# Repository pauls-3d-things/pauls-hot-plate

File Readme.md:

# SMD Soldering Station / Hotplate

**WARNING! If you have no experience wiring mains, do not proceed with this project. USE THIS INFORMATION YOUR OWN RISK!!**

## Support my projects ❤️

It takes me countless hours to prepare and document my projects. [You can support me by reading/recommending my books.](https://p3dt.net/books.html) Thank you!

## License

See `License` file. GPLv3.

## Introduction

This is a project to build a DIY PID controlled hotplate. This includes a python script to create a temperature chart and a tiny PCB to extend a TTGO 1.3" OLED shield as a controller.

- ESP8266 OLED board: https://www.aliexpress.com/item/32854542718.html
- SMD Hot plate, maybe something like this: https://www.aliexpress.com/item/1005003120565125.html
- SSR-25 DA Solid State Module
- Hot plate adapter board: see `hardware/` for KiCAD sources, or order here: https://aisler.net/p/AJJEAEVL
- 1x4.7k, 1x10k 0603 resitor
- 1x100k Thermistor (from my 3D printer)
- 2x8pin female header
- 3x2pin JST-XH 2.50mm
- Code: see `firmware/`

## Firmware
### Setup
Skip part 1 or steps 1-3 if Visual Studio Code and the extension PlatformIO have been installed.

PART 1
1) Install [Visual Studio Code](https://code.visualstudio.com) and start the application. If you have any issues installing there is plenty of resources online for help.
2) Follow this [official guide](https://docs.platformio.org/en/latest//integration/ide/vscode.html) or click on extenstions(Ctrl+Shift+X) located on the menu on the far left(the symbol looks like tetris). 
3) Type in the search bar "PlatformIO IDE", an item with an alien as a logo should be appear. Click install, this is will take a few moments and VSC will need to be reloaded after the extension has been installed.

PART 2

3) Open PlatformIO, click the button at the footer menu(bottom left) that looks like a home. This navigates to PlatformIO Home.
4) Click "Open Project" and navigate to the folder `firmware/` of this repo.
5) Click the blue button "Open "firmware"" and wait for PlatformIO to configure the workspace.
6) Plug in the ESP8266 OLED board and click the right arrow(→) button at the footer menu(bottom left). This will build and upload the firmware to the board.

The trickiest part was to get the temperature readings correct.
I had the best results using the *Stein-Hart* model to obtain correct temperature readings (which only works above 40C, but as we want to solder somethings, this should be OK ;) ). If you are using a different setup, you will need to adapt the line in `main.cpp`, using values derived with this tool: https://www.thinksrs.com/downloads/programs/therm%20calc/ntccalibrator/ntccalculator.html

```c++
SteinhartHart sh(SENSOR_PIN, 4700, 1.719817401e-3, 0.3527370551e-4, 10.70472184e-7);
```

The software has two modes: constant temperature and reflow. You can adapt the reflow curve by changing the setup code. The constructor takes the *label of the phase*, *the temperature in C*, *how long to hold the temperature in millis*, and *the kP* factor (higher value = more agressive heating = overshooting). I've set the *kP* high to quickly reach the max temp at end of the reflow phase:

```c++
void setupTempControl() {
  tempControl.add(new TempStep("heatup", HEATUP, 120, 1 * 1000, 1.0));
  tempControl.add(new TempStep("soak", HEATUP, 150, 80 * 1000, 1.5));
  tempControl.add(new TempStep("reflow", HEATUP, 230, 1 * 1000, 3.0));
  tempControl.add(new TempStep("reflow", HEATUP, 245, 3 * 1000, 10.0));
  tempControl.add(new TempStep("cooldown", COOLDOWN, 50, 10 * 1000));
}
```

## Hardware

The overall setup *could* look like this, the setup below is only for educational purposes:

**DO NOT LEAVE THE MAINS VOLTAGE TERMINALS EXPOSED!!**

I used the following adapter to connect everything to the EPS8266 board:

The schematics:

## serial-plotter

Requires Python

```bash
pip3 install matplotlib
pip3 install pyserial
```

Usage:

```bash
python3 main.py /dev/cu.usb... 115200
```

### On Error: can't import serial

If the `import serial` fails

```bash
pip3 uninstall serial
pip3 uninstall pyserial

pip3 install pyserial
```

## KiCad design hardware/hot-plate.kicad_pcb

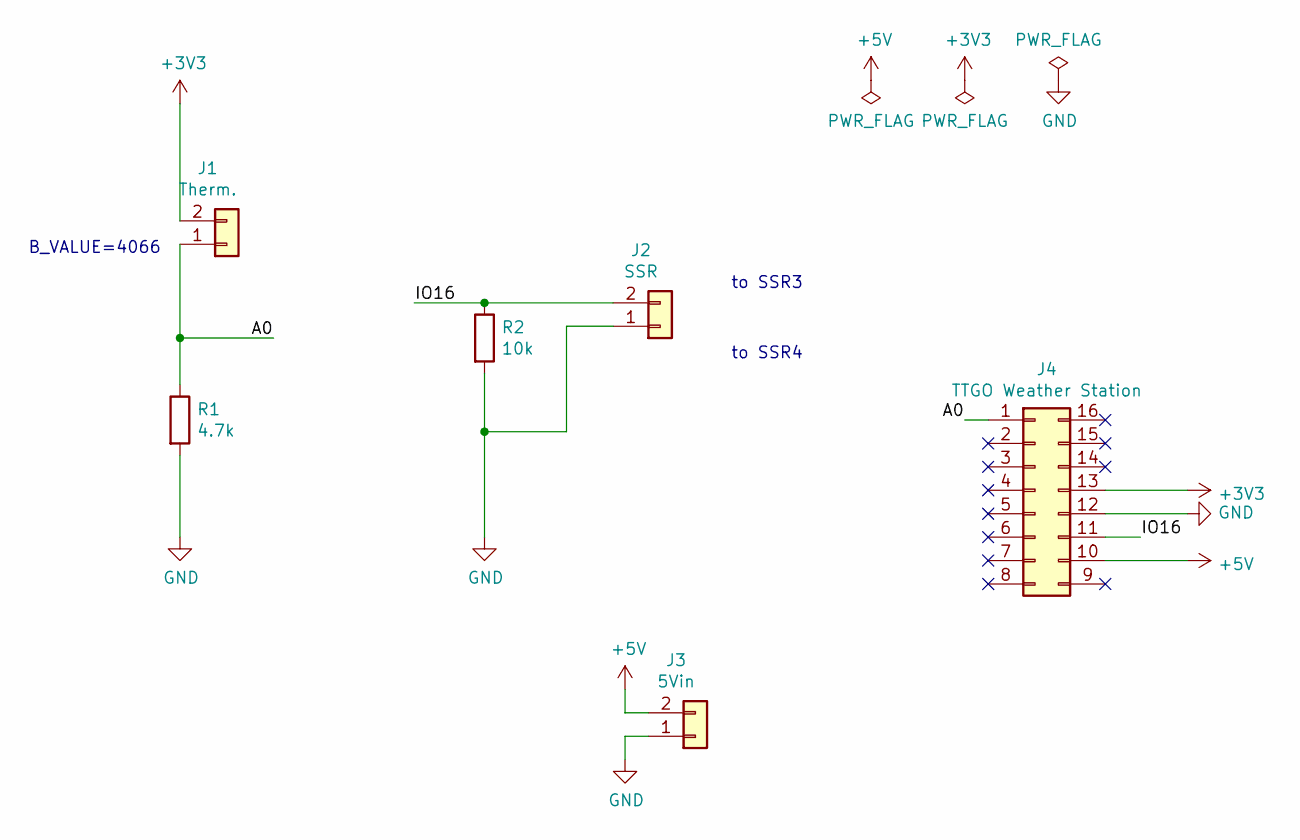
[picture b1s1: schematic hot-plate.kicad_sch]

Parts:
J1: Therm.; JST_XH_B2B-XH-A_1x02_P2.50mm_Vertical
J2: SSR; JST_XH_B2B-XH-A_1x02_P2.50mm_Vertical
J3: 5Vin; JST_XH_B2B-XH-A_1x02_P2.50mm_Vertical
J4: TTGO Weather Station; PinHeader_2x08_P2.54mm_Vertical
R1: 4.7k; R_0603_1608Metric_Pad1.05x0.95mm_HandSolder
R2: 10k; R_0603_1608Metric_Pad1.05x0.95mm_HandSolder

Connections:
+3V3: J1.2, J4.13
+5V: J3.2, J4.10
/A0: J1.1, J4.1, R1.1
/IO16: J2.2, J4.11, R2.1
GND: J2.1, J3.1, J4.12, R1.2, R2.2

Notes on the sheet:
B_VALUE=4066
to SSR3
to SSR4

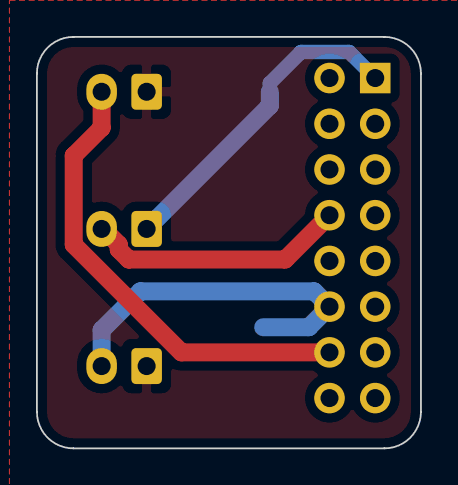
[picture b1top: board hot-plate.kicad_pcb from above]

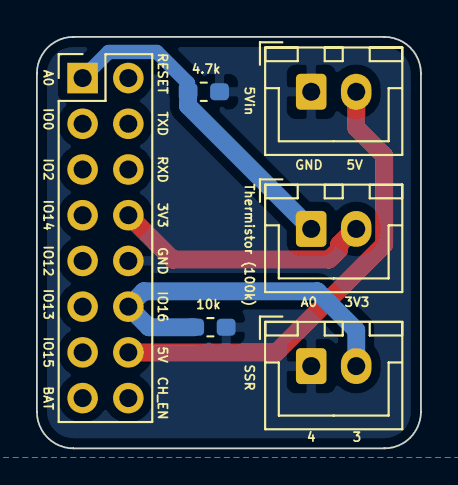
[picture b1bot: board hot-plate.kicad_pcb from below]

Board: 2 copper layers, 21.3 x 22.9 mm, 6 parts (6 on the bottom side), 5 nets.

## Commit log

2022-04-24 Readme.md: fix typo
2022-04-24 Readme.md: add vsc info
2022-04-24 rm .DS_Stores
2022-04-24 add License info
2022-05-19 Update Readme.md
    Added how to set up the environment and upload firmware to the board.
